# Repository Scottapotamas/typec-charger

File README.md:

# typec-charger
USB Type C charger for laptops or phones, that uses generic DC inputs as the source.

# Requirements & Goals

Create a DC-DC charger that uses USBc PD as the delivery mechanism. 
Aim to support the widest range of devices possible (including my Dell XPS 9550).

Run off Li-Poly or Li-Ion cells or similar sources. This could include car batteries (directly or from cigarette lighter socket), and other sources. 
This is useful when taking devices to the field, or allows a comodity pouch cell battery to act as a bulk battery bank.
 
- Accept wide input range sources, 10V to 26V operating input (3S to 6S lithium, includes 12V and 24V automotive).
- Use XT60? input to allow direct lipo connectors or existing COTS cables with aligators etc.

- Input must be ESD protected and filtered.
- Input must have reverse polarity protection, and overvoltage up to 30V DC.
- Device must indicate that a power source has been applied.
- Device should include visual indication that battery is low.
- Device should include battery voltage low-cutoff to prevent over-discharge of source.

- Output USB 3.1 C Power Delivery 2.0 Compliant charging power (5, 9, 12, 20V) at up to 3A. Consider 5A as optional expansion?
- USB Type C socket on the charger, to allow users to find their own cable. No integrated cable tail.
- Compatibility with Dell XPS, Apple Macbook Pro, and other devices.
- Compatibility with USB-C fast charging phones if possible.
- Compatiblity with USB2 charging devices as part of compatibility mode (via 3.1C -> 2.0 MicroB cable).
- It is desirable that the charger supports greater than 60W charging for faster charge on performance laptops.
- Output should be ESD Protected and feature filtering for EMI.

- Where practical, x/y/z dimensions should be minimised for tight form factor.
- The device's enclosure should not exceed 50C at steadystate for a 'full load'.
- The device should not emit any audible noice (coil whine etc) which can be heard in a quite space (<25dB?)
- The product should aim to meet applicable EMC standards (class 2, non-intentional radiator), use spec analyser at work to validate.

Ideally this solution costs less than $100AU (not including charge cable or batteries). This would price it under or around the Apple 61W and 87W chargers, or the Chromebook Pixel 60W charger after importing to AUS. 

- Manufacturing cost of assembled PCB is less than $60USD.
- Manufacturing cost of enclosure less than $20USD.
- Manufacturing cost of packaging (box, manual, etc) less than $5USD.

# Testing and Implementation Notes

- Wide input power supply low voltage cutoff set at just under 9V. This is the extent of low battery protection, not using anything smarter.
- Currently there is no additional 3 or 5V reg, which means there isn't any stable voltage. Any additional circuitry has to either support 5-20V or include regulation.
- Input protection circuit is beefy. Confidence in the charger is important, especially with all the press going on with USBC non-compliant chargers.
- Battery indication led was really hard to get worked out. Uses a SMD led and lightpipe for charging status. Might remove this for production.
- Board has been made as small as possible to fit in the example extrusion.
- Power dissipation for power supply stage is worst case 1.7W between all parts. Worst part is switching fet at 650mW. Consider heatsink or thermal transfer to case?
- Validate thermal performance with thermal camera.
- XT60 connector is too high for normal mounting. Consider using a second PCB to drop the height to the center of the extrusion or a different connector.
- Greater than 3A is supported with switch.
- Power limit set to ~60W default, switch will allow ~90W.
- 5A is possible to be selected without the 90W expansion (5/12V devices)

# Manufacturability

- Board is a 4 layer pcb with single sided population. All parts are SMD.
- Small form factor means small boxes and packaging requirements.
- Consider enclosures 
	- https://www.aliexpress.com/store/product/4-pcs-electronics-aluminum-enclosure-boxes-13-60-50mm-2015-aluminum-powder-coating-project-box-aluminum/1006252_32312473247.html?spm=2114.12010612.0.0.7DTtvx
	- https://www.aliexpress.com/item/1-piece-szomk-aluminum-project-box-100-60-13mm-enclosures-for-electronics-electronic-2014-new-aluminum/32241037210.html

5 Prototype boards have been ordered for PCBA. Cost per board is just under 60USD at current.

# Device Compatibility

- Dell XPS didn't like negotiation stage where eval board sat at 12V for a few hundred milliseconds. Disabling 12V and going from 5->20V works fine.
- Investigate XPS when the 5V and 20V are done by same regulator instead of two-stage.
- Dell XPS will charge on lower currents as long as the charger is advertising at least 60W.
- Haven't been able to get more than 61W draw from the XPS, regardless of BIOS settings.

- Nintendo Switch uses the 15V standard which the main model of this charger is not designed for.
- The Switch will charge with 5V 3A though.
- People in https://www.reddit.com/r/NintendoSwitch/comments/5x948s/answering_your_questions_about_usb_typec/ say that the Switch uses 12V as fallback from 15V.

- Supports BC1.2 charging for legacy USB2 devices at up to 2A.
- Charges phones fine at 10W over a USBC-MicroB cable.
- Should support most phones properly with 5V 3A charging over TypeC.

# Sale Notes

Sell it as a standalone device with the option of adding the following:

- Barrel to XT60 connector
- Barrel to Aligator clips
- Barrel to cigarette lighter
- Barrel to D-Tap
- Barrel to ring terminals?

Device should also include some packaging and a card describing the specifications etc.

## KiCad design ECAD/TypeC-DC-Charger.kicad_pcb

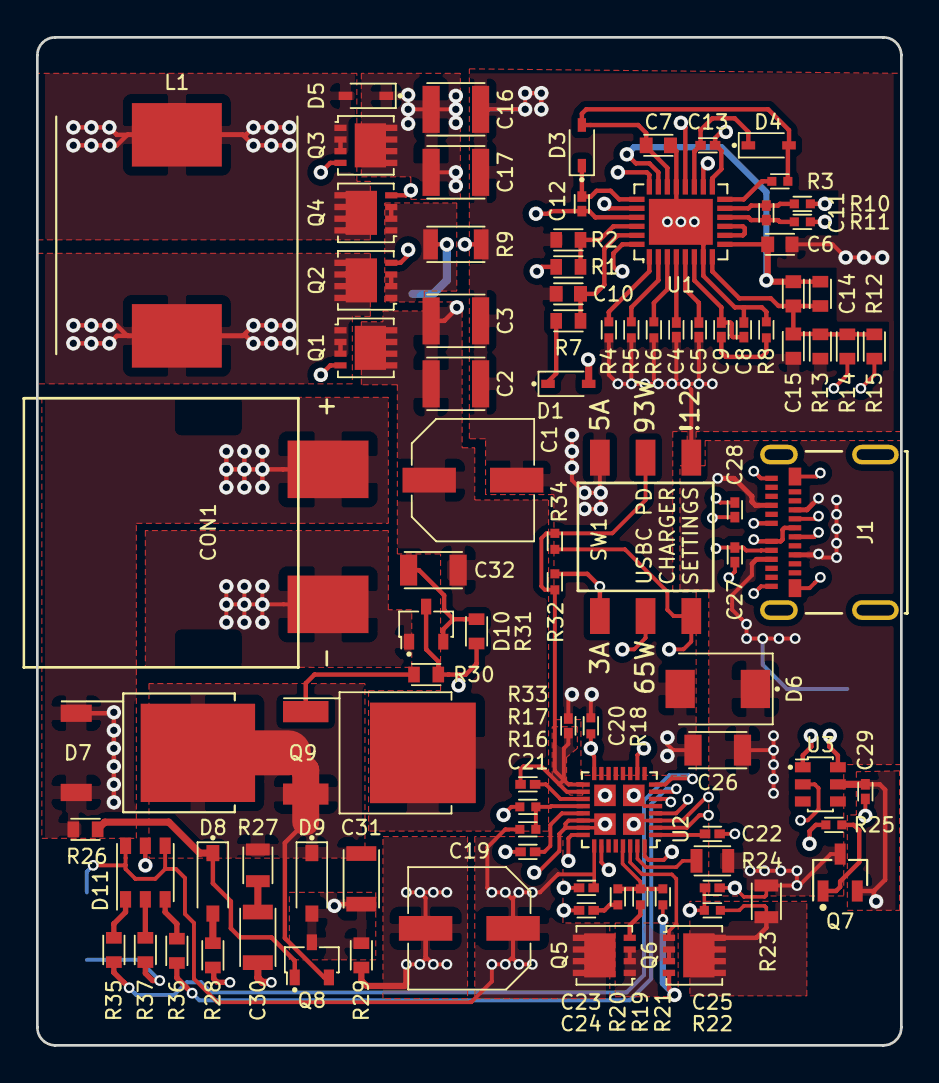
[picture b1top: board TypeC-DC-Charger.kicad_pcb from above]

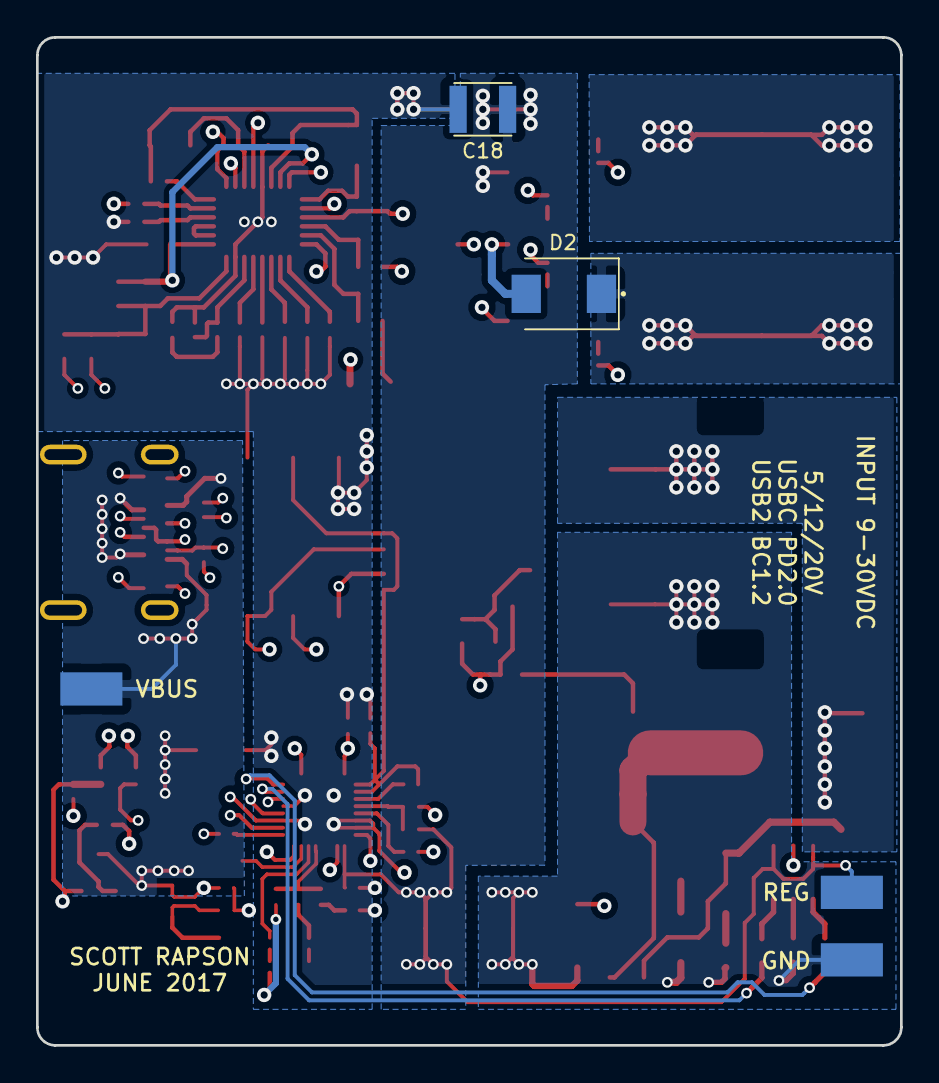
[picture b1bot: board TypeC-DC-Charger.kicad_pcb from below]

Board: 4 copper layers, 48.0 x 56.0 mm, 99 parts (5 on the bottom side), 65 nets.

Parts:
C1, C19: 100UF_ELEC_35V_660X580M; CAPAE660X580DD180L260L
C2, C3: 10UF_X7S_3225M; CAPC3225X170L
C4, C8: 100PF_C0G_1005M; CAPC1005X60L
C5, C12, C13, C21, C22, C23, C29: 100NF_X7R_1005M; CAPC1005X60L
C6, C7: 1UF_X7R_1608M; CAPC1608X90L
C9: 22NF_X7R_1005M; CAPC1005X60L
C10, C15: 100NF_X7R_1608M; CAPC1608X90L
C11: 47PF_X7R_1005M; CAPC1005X60L
C14: 22NF_X7R_1608M; CAPC1608X90L
C16, C17, C18: 22UF_X7R_3225M; CAPC3225X170L
C20, C25: 330NF_X5R_1005M; CAPC1005X60L
C24: 10NF_X7R_1005M; CAPC1005X60L
C26: 6.8UF_X7R_3216M; CAPC3216X135L
C27, C28: 330PF_X7R_1005M; CAPC1005X60L
C30, C31: 1UF_X7R_3216M; RESC3216X60L
C32: 100NF_X7R_3216M; CAPC3216X135L
CON1: XT60-PT-MALE
D1, D3, D4, D5: 40V_500mA_SOD323; SOD2512X110L
D2: CD214B-B250LF; SODFL5436X262L
D6: SSB44-E3/52T_DO214AA; SODFL5436X262L
D7: 300V_10A_DPAK; TO440P972X240-3N
D8, D9: 33V_500mW_SOD123; SOD3715X145L
D10: BAV99; SOT95P240X110-3L16L
D11: LED_RGB_PLCC6; PLCC110P330X340X200-8L
J1: USB_C_SOCKET_RA_SMD; MOLEX-105450-0101
L1: 3.3uH_5050M; INDM132129X500N
Q1, Q2: CSD18543Q3A; SON65P315X300X90-9T174X245L
Q3, Q4: CSD17551Q3A; SON65P315X300X90-9T174X245L
Q5, Q6: CSD17579Q3A; SON65P315X300X90-9T174X245L
Q7: 2N7002P; SOT95P240X110-3L16N
Q8: BC857B; SOT95P240X110-3L16L
Q9: IRFR9024NTRPBF; DPAK4P229_990X239L159X95L
R1: 249K_1608M; RESC1608X50L
R2: 41K2_1608M; RESC1608X50L
R3, R8: 10K_1005M; RESC1005X40L
R4: 93K1_1005M; RESC1005X40L
R5: 0R_1005M; RESC1005X40L
R6: 84K5_1005M; RESC1005X40L
R7, R30: 10R_1608M; RESC1608X50L
R9: 0.01R_3216M; RESC3216X60L
R10, R11: 100R_1005M; RESC1005X40L
R12: 49K9_1608M; RESC1608X50L
R13: 9K53_1608M; RESC1608X50L
R14: 4K99_1608M; RESC1608X50L
R15: 5K76_1608M; RESC1608X50L
R16: 1M_1005M; RESC1005X40L
R17: 680K_1005M; RESC1005X40L
R18: 100K_1005M; RESC1005X40L
R19, R21, R22, R25: 10R_1005M; RESC1005X40L
R20: 1K_1005M; RESC1005X40L
R23: 0.005R_2012M; RESC2012X50L
R24: 120R_2012M; RESC2012X50L
R26: 100K_1608M; RESC1608X50L
R27: 10R_2012M; RESC2012X50L
R28: 22K_1608M; RESC1608X50L
R29: 332K_1608M; RESC1608X50L
R31: 10K0_1608M; RESC1608X50L
R32, R34: 220K_1005M; RESC1005X40L
R33: 0R_1005M; CAPC1005X60L
R35: 1K50_1608M; RESC1608X50L
R36: 2K40_1608M; RESC1608X50L
R37: 330R_1608M; RESC1608X50L
SW1: 2.54mm_3xSPST_SMD; MCEMR-03-T
TEST2, TEST3, TEST5: PROBE_HOOK; HARWIN_S1751-46
U1: LM5175RHF; QFN50P500X400X100-29T255X355N
U2: TPS25741; QFN40P400X400X100-33T280N
U3: TPS2514; SOT95P240X110-6L16L

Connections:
5V: C29.1, D11.A2, Q7.2, U3.5
/Connectors/RAW_BATT: CON1.2, D7.A, R26.2
/Power Supply/VCC: C7.1, D3.A, D4.A, R3.2, U1.20
/USBC Controller/DVDD: C20.1, R32.1, R33.1, R34.1, SW1.4, U2.17, U2.18
/USBC Controller/EN12V: R34.2, SW1.5, U2.10
/USBC Controller/HIPWR: R32.2, SW1.1, U2.6
/USBC Controller/PSEL: R18.2, SW1.3, U2.16
CC1: C27.1, J1.A5, U2.2
CC2: C28.1, J1.B5, U2.4
CTRL1: R14.2, R36.2, U2.7
CTRL2: R15.2, R35.2, U2.8
D+: J1.A6, J1.B6, U3.1
D-: J1.A7, J1.B7, U3.6
DSCG: R24.2, U2.31
FB: C14.2, C15.1, R12.2, R13.1, R14.1, R15.1, U1.8
G5V: R25.2, U2.32
GDNG: R19.2, R20.1, R21.2, U2.29
GDNS: Q5.2, Q6.2, U2.30
GND: C1.2, C2.2, C3.2, C4.2, C5.2, C6.2, C7.2, C8.2, C10.1, C15.2, C16.2, C17.2, C18.2, C19.2, C20.2, C21.2, C22.2, C23.2, C24.2, C26.2, C27.2, C28.2, C29.2, C30.2, CON1.1, D6.A, D10.1, J1.A1, J1.A12, J1.B1, J1.B12, J1.S1, J1.S2, J1.S3, J1.S4, R2.2, R4.2, R5.2, R6.2, R8.2, R9.1, R11.1, R13.2, R17.2, R18.1, R28.2, R29.2, R37.2, SW1.2, SW1.6, TEST5.1, U1.7, U1.19, U1.29, U2.3, U2.5, U2.22, U2.23, U2.33, U3.2
HDRV1: Q1.1, U1.24
HDRV2: Q3.1, U1.16
ISNS: C25.1, R22.2, U2.24
LDRV1: Q2.1, U1.22
LDRV2: Q4.1, U1.18
unnamed: C4.1, U1.4
unnamed: C5.1, U1.5
unnamed: C8.1, C9.1, U1.6
unnamed: C9.2, R8.1
unnamed: C10.2, R7.2, U1.27
unnamed: C11.1, R10.2, U1.13
unnamed: C11.2, R11.2, U1.12
unnamed: C12.1, D3.C, U1.23
unnamed: C13.1, D4.C, U1.17
unnamed: C21.1, U2.21
unnamed: C22.1, U2.1
unnamed: C24.1, R20.2
unnamed: C30.1, R27.2
unnamed: C31.1, D7.C, D9.C, Q8.2, Q9.3, R27.1
unnamed: C31.2, D9.A, D10.3, Q8.3, R29.1, R30.2, R31.2
unnamed: C32.2, D10.2, R31.1
unnamed: D1.C, R7.1
unnamed: D8.A, R28.1
unnamed: D8.C, Q8.1, R26.1
unnamed: D11.C1, R35.1
unnamed: D11.C2, R37.1
unnamed: D11.C3, R36.1
unnamed: Q5.1, R19.1
unnamed: Q6.1, R21.1
unnamed: Q6.3, R22.1, R23.2
unnamed: Q7.1, R25.1
unnamed: Q9.1, R30.1
unnamed: R1.2, R2.1, U1.26
unnamed: R3.1, U1.14
unnamed: R4.1, U1.1
unnamed: R5.1, U1.2
unnamed: R6.1, U1.3
unnamed: R16.2, R17.1, U2.20
unnamed: R33.2, U2.19
unnamed: U1.10, U1.11
RCS: D2.A, Q2.2, Q4.2, R9.2, R10.1
SW1: C12.2, D2.C, L1.2, Q1.2, Q2.3, U1.25
SW2: C13.2, D5.A, L1.1, Q3.2, Q4.3, U1.15
VARIABLE_DC: C6.1, C14.1, C16.1, C17.1, C18.1, C19.1, C23.1, D5.C, D11.A1, D11.A3, Q3.3, Q5.3, R12.1, R16.1, TEST2.1, U1.9, U1.21, U2.25
VBUS: C25.2, C26.1, D6.C, J1.A4, J1.A9, J1.B4, J1.B9, Q7.3, R23.1, R24.1, TEST3.1, U2.26
VIN: C1.1, C2.1, C3.1, C32.1, D1.A, Q1.3, Q9.4, R1.1, U1.28

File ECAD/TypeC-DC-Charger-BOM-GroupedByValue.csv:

"Title:",""
"Rev:",""
"Source:","F:\Projects\typec-charger\ECAD\TypeC-DC-Charger.sch"
"Date:","5/05/2017 1:24:09 AM"
"Component Count:","92"

"Ref","Qty","Value","Description","Manf","Manf#","Installed","Footprint"
"C1, C19","2","100UF_ELEC_35V_660X580M","CAP, ALU ELEC, 100UF, 35V, SMD","PANASONIC","EEEFT1V101AP"," ","CAPAE660X580DD180L260L"
"C10, C15","2","100NF_X7R_1608M","CAP, MLCC, X7R, 100NF, 50V, 0603","KEMET","C0603C104K5RACAUTO"," ","CAPC1608X90L"
"C11","1","47PF_X7R_1005M","CAP, MLCC, X7R, 47PF, 50V, C0G, 0402, 1005M","MULTICOMP","MC0402N470K500CT"," ","CAPC1005X60L"
"C14","1","22NF_X7R_1608M","CAP, MLCC, X7R, 22NF, 50V, 0603, 1608M","MULTICOMP","MC0603B223K500CT"," ","CAPC1608X90L"
"C16, C17, C18","3","22UF_X7R_3225M","CAP, MLCC, X7R, 22UF, 25V, 10%, 1210, 3225M","MURATA","C1210C226K3RACTU"," ","CAPC3225X170L"
"C2, C3","2","10UF_X7S_3225M","CAP, MLCC, X7R, 10UF, 50V, 1210 3225M","TDK","C3225X7S1H106M250AB"," ","CAPC3225X170L"
"C20, C25","2","330NF_X5R_1005M","CAP, MLCC, X5R, 330NF, 25V, 0402, 1005M","TDK","C1005X5R1E334K050BB"," ","CAPC1005X60L"
"C24","1","10NF_X7R_1005M","CAP, MLCC, X7R, 10NF, 50V, 0402, 1005M","KEMET","C0402C103K5RACTU"," ","CAPC1005X60L"
"C26","1","6.8UF_X7R_1608M","CAP, MLCC, X7R, 6.8UF, 50V, 0603","TDK","C1608X5R1A685K080AC"," ","CAPC1608X90L"
"C27, C28","2","330PF_X7R_1005M","CAP, MLCC, X7R, 330PF, 50V, 0402, 1005M","MURATA","GRM155R71H331KA01D"," ","CAPC1005X60L"
"C30, C31","2","1UF_X7R_3216M","CAP, MLCC, X7R, 1UF, 100V, 1206, 3216M","TDK","C3216X7R2A105K160AA"," ","RESC3216X60L"
"C32","1","100NF_X7R_3216M","CAP, MLCC, X7R, 100nF, 100V, 1206, 3216M","YAGEO","CC1206KKX7R0BB104"," ","CAPC3216X135L"
"C4, C8","2","100PF_C0G_1005M","CAP, MLCC, X7R, 100PF, 50V, 0402, 1005M","MURATA","GCM1555C1H101JA16D"," ","CAPC1005X60L"
"C5, C12, C13, C21, C22, C23, C29","7","100NF_X7R_1005M","CAP, MLCC, X7R, 100NF, 50V, 0402, 1005M","TDK","CGA2B3X7R1H104K050BB"," ","CAPC1005X60L"
"C6, C7","2","1UF_X7R_1608M","CAP, MLCC, X7R, 1UF, 50V, 0603","MURATA","GRM188R61H105KAALD"," ","CAPC1608X90L"
"C9","1","22NF_X7R_1005M","CAP, MLCC, X7R, 22NF, 50V, 0402, 1005M","MURATA","GRM155R71H223KA12D"," ","CAPC1005X60L"
"CON1","1","XT60-PT-MALE","XT60PT, 3.5mm Banana Connector Style, Plug, Male, SMD","AMASS","XT60PT-M"," ","XT60-PT-MALE"
"D1, D3, D4, D5","4","40V_500mA_SOD323","DIODE SCHOTTKY 40V 500MA 470mV Fwd SOD323","NXP","PMEG4005AEA"," ","SOD2512X110L"
"D10","1","BAV99","DIODE DUAL, 100V, 215mA, 4ns, SOT23","NXP","BAV99"," ","SOT95P240X110-3L16L"
"D2","1","CD214B-B250LF","DIODE, CHIP, 50V, 2A, DO-214AA","BOURNS","CD214B-B250LF"," ","SODFL5436X262L"
"D6","1","SSB44-E3/52T_DO214AA","DIODE, Schottky, 40V, 4A, 10ns, SMB, DO-214AA","VISHAY","SSB44-E3/52T"," ","SODFL5436X262L"
"D7","1","300V_10A_DPAK","DIODE, 10A cont, 20A, 300V, 13ns, 0.9V, DPAK","ST","STTH1003SBY-TR"," ","TO440P972X240-3N"
"D8, D9","2","33V_500mW_SOD123","DIODE, Zener 33V, 500mW, SOD123","VISAY SEMICONDUCTOR","BAT41ZFILM"," ","SOD3715X145L"
"J1","1","USB_C_SOCKET_RA_SMD","USB Type C Recep, Female, R/A, TOPMNT, GLD Flash, 24 contact, 5A","Molex","105450-0101"," ","MOLEX-105450-0101"
"L1","1","3.3uH_5050M","IHLP5050EZ, INDUCTOR, 3.3UH, 15A, Shielded, 0.0092ohm, 20%,","VISHAY","IHLP5050EZER3R3M01"," ","INDM132129X500N"
"Q1, Q2","2","CSD18543Q3A","POWER MOSFET, N-CH, NexFET, 60Vds, 20Vgs, 35A, 8.1mOhm, 1.7nC gd, 2.0Vgs, SON","TI","CSD18543Q3A"," ","SON65P315X300X90-9T174X245L"
"Q3, Q4","2","CSD17551Q3A","POWER MOSFET, N-CH, NexFET, 30Vds, 20Vgs, 20A, 7.8mOhm, 1.5nC gd, 1.6Vgs, SON","TI","CSD17551Q3A"," ","SON65P315X300X90-9T174X245L"
"Q5, Q6, Q7","3","CSD17579Q3A","POWER MOSFET, N-CH, NexFET, 30Vds, 20Vgs, 20A, 8.7mOhm, 1.2nC gd, 1.5Vgs, SON","TI","CSD17579Q3A"," ","SON65P315X300X90-9T174X245L"
"Q8","1","BC857B","Transistor, PNP 45V, 100mA, 250mW, SOT23","MULTICOMP","BC857B"," ","SOT95P240X110-3L16L"
"Q9","1","IRFR9024NTRPBF","MOSFET P-CH 55V 11A DPAK TO-252AA","Infineon","IRFR9024NTRPBF"," ","DPAK4P229_990X239L159X95L"
"R1","1","249K_1608M","RESISTOR, THICK FILM, 249K, 100mW, 1%, 0603, 1608M","VISHAY","CRCW0603249KFKEA"," ","RESC1608X50L"
"R10, R11","2","100R_1005M","RESISTOR, THICK FILM, 100R, 63mW, 1%, 0402, 1005M","VISHAY","CRCW0402100RFKED"," ","RESC1005X40L"
"R12","1","49K9_1608M","RESISTOR, THICK FILM, 49.9K, 100mW, 1%, 0603, 1608M","VISHAY","CRCW060349K9FKEA"," ","RESC1608X50L"
"R13","1","9K53_1608M","RESISTOR, THICK FILM, 9.53K, 100mW, 1%, 0603, 1608M","VISHAY","CRCW06039K53FKEA"," ","RESC1608X50L"
"R14","1","4K99_1608M","RESISTOR, THICK FILM, 4.99K, 100mW, 1%, 0603, 1608M","VISHAY","MCT06030C4991FP500"," ","RESC1608X50L"
"R15","1","5K76_1608M","RESISTOR, THICK FILM, 5.76K, 100mW, 1%, 0603, 1608M","PANASONIC","ERJ3EKF5761V"," ","RESC1608X50L"
"R16","1","1M_1005M","RESISTOR, THICK FILM, 1MOhm, 63mW, 1%, 0402, 1005M","VISHAY","CRCW04021M00FKED"," ","RESC1005X40L"
"R17","1","680K_1005M","RESISTOR, THICK FILM, 680K, 100mW, 1%, 0402, 1005M","PANASONIC","ERJ2RKF6803X"," ","RESC1005X40L"
"R18","1","100K_1005M","RESISTOR, THICK FILM, 100K, 100mW, 1%, 0402, 1005M","PANASONIC","ERJ2RKF1003X"," ","RESC1005X40L"
"R19, R21, R22, R25, R30","5","10R_1005M","RESISTOR, THICK FILM, 10R, 63mW, 1%, 0402, 1005M","VISHAY","CRCW040210R0FKED"," ","RESC1005X40L"
"R2","1","41K2_1608M","RESISTOR, THICK FILM, 41.2K, 200mW, 0603, 1608M","PANASONIC","ERJP03F4122V"," ","RESC1608X50L"
"R20","1","1K_1005M","RESISTOR, THICK FILM, 1K, 63mW, 1%, 0402, 1005M","VISHAY","CRCW04021K00FKED"," ","RESC1005X40L"
"R23","1","0.005R_2012M","RESISTOR, THICK FILM, 5mOhm, 500mW, 1%, 0805, 2012M","WALSIN","WW08RR005FTL"," ","RESC2012X50L"
"R24","1","120R_2012M","RESISTOR, THICK FILM, 120R, 500mW, 5%, 0805, 2012M","PANASONIC","ERJ-P06J121V"," ","RESC2012X50L"
"R26","1","100K_1608M","RESISTOR, THICK FILM, 100K, 125mW, 1%, 0603, 1608M","MULTICOMP","MC0063W06035100K"," ","RESC1608X50L"
"R27","1","10R_2012M","RESISTOR, THICK FILM, 10R, 125mW, 1%, 0805, 2012M","PANASONIC","ERJ8ENF10R0V"," ","RESC2012X50L"
"R28","1","22K_1608M","RESISTOR, THICK FILM, 22K, 100mW, 1%, 0603, 1608M","MULTICOMP","MCMR06X2202FTL"," ","RESC1608X50L"
"R29","1","332K_1608M","RESISTOR, THICK FILM, 332K, 250mW, 0603, 1608M","PANASONIC","ERJPA3F3323V"," ","RESC1608X50L"
"R3, R8","2","10K_1005M","RESISTOR, THICK FILM, 10K, 63mW, 1%, 0402, 1005M","VISHAY","CRCW040210K0FKED"," ","RESC1005X40L"
"R31","1","10K0_1608M","RESISTOR, THICK FILM, 10K, 125mW, 1%, 0603, 1608M","TE CONNECTIVITY","CRGH0603F10K"," ","RESC1608X50L"
"R4","1","93K1_1005M","RESISTOR, THICK FILM, 93.1K, 100mW, 1%, 0402, 1005M","PANASONIC","ERJ2RKF9312X"," ","RESC1005X40L"
"R5","1","0R_1005M","RESISTOR, THICK FILM, 0R, 63mW, 1%, 0402, 1005M","VISHAY","CRCW04020000Z0ED"," ","RESC1005X40L"
"R6","1","84K5_1005M","RESISTOR, THICK FILM, 84.5K, 63mW, 1%, 0402, 1005M","PANASONIC","ERA2AEB8452X"," ","RESC1005X40L"
"R7","1","10R_1608M","RESISTOR, THICK FILM, 10R, 125mW, 0603, 1608M","MULTICOMP","MCHP03W8F100JT5E"," ","RESC1608X50L"
"R9","1","0.01R_3216M","RESISTOR, THICK FILM, 10mOhm, 1W, 1206, 3216M","Vishay","WSLP1206R0100FEA"," ","RESC3216X60L"
"TEST2, TEST3, TEST4, TEST5","4","PROBE_HOOK","PCB Probe Hook SMD","HARWIN","S1751-46R"," ","HARWIN_S1751-46"
"U1","1","LM5175RHF","4-Switch Synchronous Buck-Boost Controller, 3.5-42V IN, 0.8-55V OUT, <600kHz, VQFN-28","TEXAS INSTRUMENTS","LM5175RHFR"," ","QFN50P500X400X100-29T255X355N"
"U2","1","TPS25741","USB 3.1 Type C and USB PD 2.0 Delivery Port Control IC, 5/12/20V 15-100W, internal 1.8V 35mA, QFN 32 with pad","TEXAS INSTRUMENTS","TPS24741"," ","QFN40P400X400X100-33T280N"
"U3","1","TPS2514","TPS251xx USB, Dedicated Charging Port Controller, BC1.2 auto detect, SOT23-6","TI","TPS2514DBVR"," ","SOT23-6P65_210X100L36X22L"

"Tool:","Eeschema (2017-03-19 revision 2637835a1)-makepkg"
"Script:","F:\Projects\ECAD\KiCad\scripts\BOM\bom\BOM-GroupedByValue.py"

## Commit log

2017-04-22 Pulling ideas from head to readme.md
2017-04-22 KiCAD project creation. Added USBC charge IC, connector, and regulator IC
2017-04-25 Started building out required parts and began wiring schematic.
2017-04-25 Schematic development for charger and usbc hardware
2017-04-29 Drew aluminium extrusion profile currently under consideration
2017-04-29 Split schematic into multiple sheets, added remaining regulator parts, cleanups and other additions.
2017-04-29 Additional cleanup and misc notes
2017-04-30 Updated links and details in readme
2017-04-30 Added shorter 50mm version of extrusion model as board looks like it could fit
2017-04-30 Soft start circuit, Switched BC1.2 IC, more 0402 parts now, placement and routing.
2017-04-30 Update to soft start circuit
2017-05-01 Changed some parts to 0402, routing and pour improvements
2017-05-04 Added better input protection with soft start, over voltage protection, cap discharge etc. Fixed some part selections, reformatting in schematic. Placement of input protection circuit. Cleanup of PCB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
2017-05-04 Fixed some newer designator labels incorrect font size
2017-05-04 Updated readme with current thoughts
2017-05-07 Added dip switch selection to charge settings. PCB placement improvements. Added 3mm led placeholder for indicator led.
2017-05-07 Silkscreen text for dip switches, part placement improvements.
2017-05-14 Added left over cad files
2017-05-21 Updated pcb files
2017-05-22 Adding vias on thermal planes
2017-05-22 Vias and power supply signal routing
2017-05-22 Routing signals and more power planes and misc
2017-05-23 RGB led added. Routing and pours. Removed some DRC errors, fixed cosmetics.
2017-05-30 Updates to schematic and pcb (led and routing)
2017-05-31 Routing and fixed dip switch disassociated footprint
2017-05-31 RGB led final schematic drawing and prelim resistor selection. Routing and misc board level changes.
2017-05-31 Routing and cosmetics
2017-06-01 Routing improvements. Silkscreen text and dimensions added. General review of placement and fixes as found.
2017-06-03 Planes, improving pours and routing. Obsessing over small details.
2017-06-03 Finishing touches for pcb
2017-06-05 Added Production outputs
2017-06-05 PCB title block text
2017-06-10 Updated readme with image and notes
2017-06-10 Revert "Updated readme with image and notes"
    This reverts commit 92b9ada7cdd4b80bd646bb17f45bc344f14f1802.
